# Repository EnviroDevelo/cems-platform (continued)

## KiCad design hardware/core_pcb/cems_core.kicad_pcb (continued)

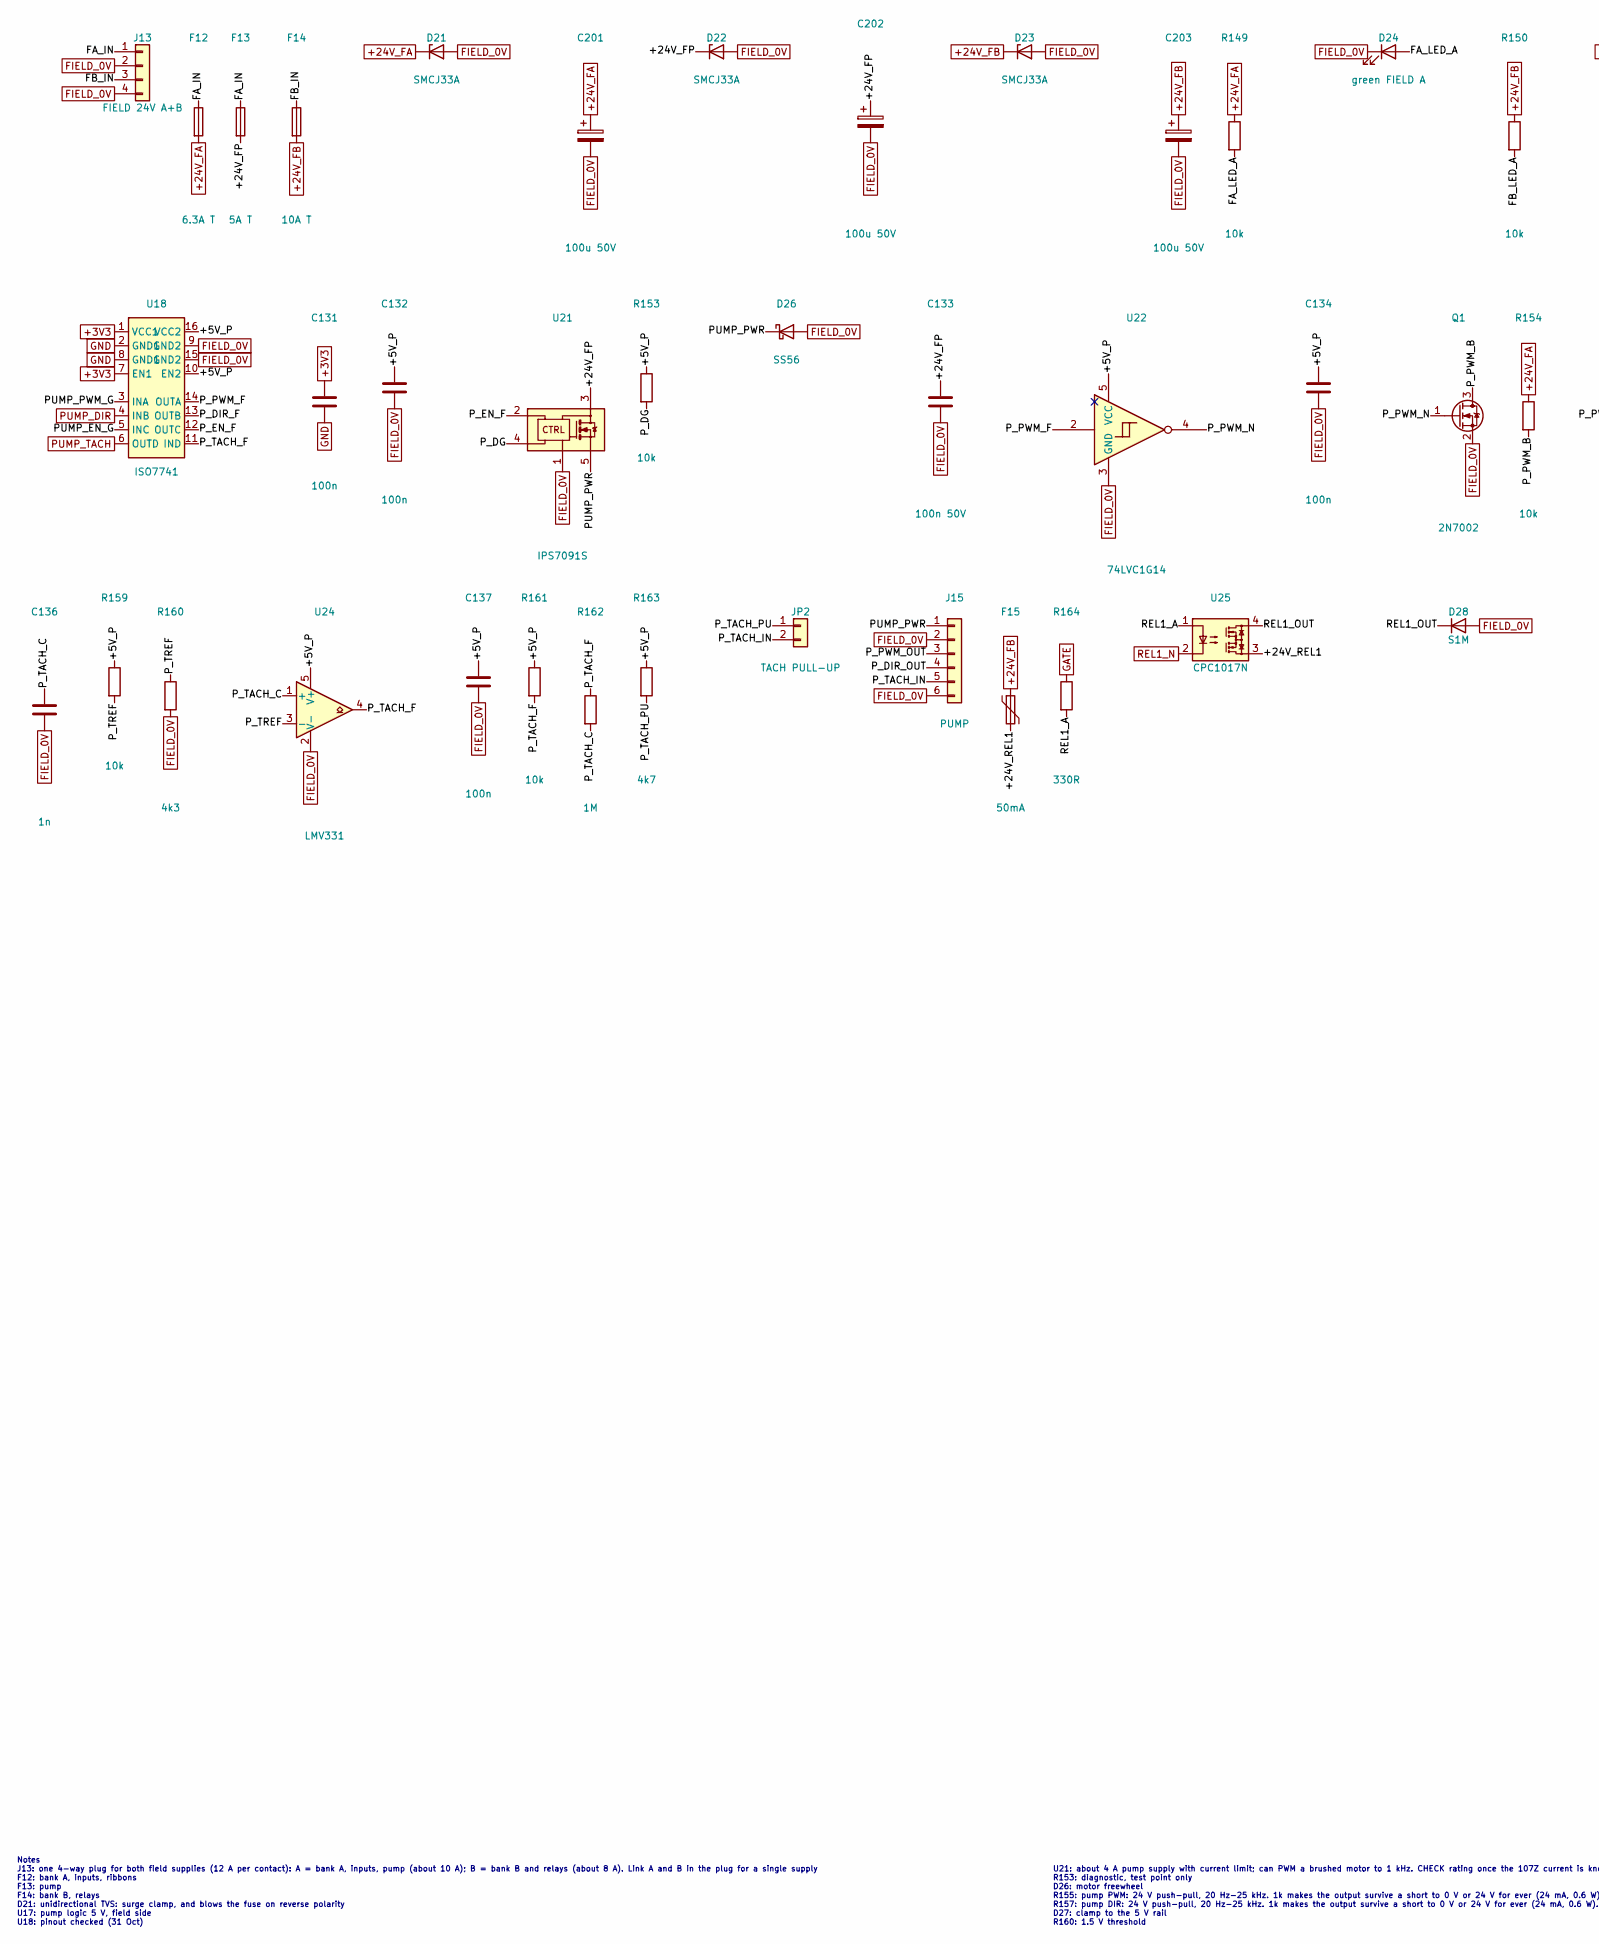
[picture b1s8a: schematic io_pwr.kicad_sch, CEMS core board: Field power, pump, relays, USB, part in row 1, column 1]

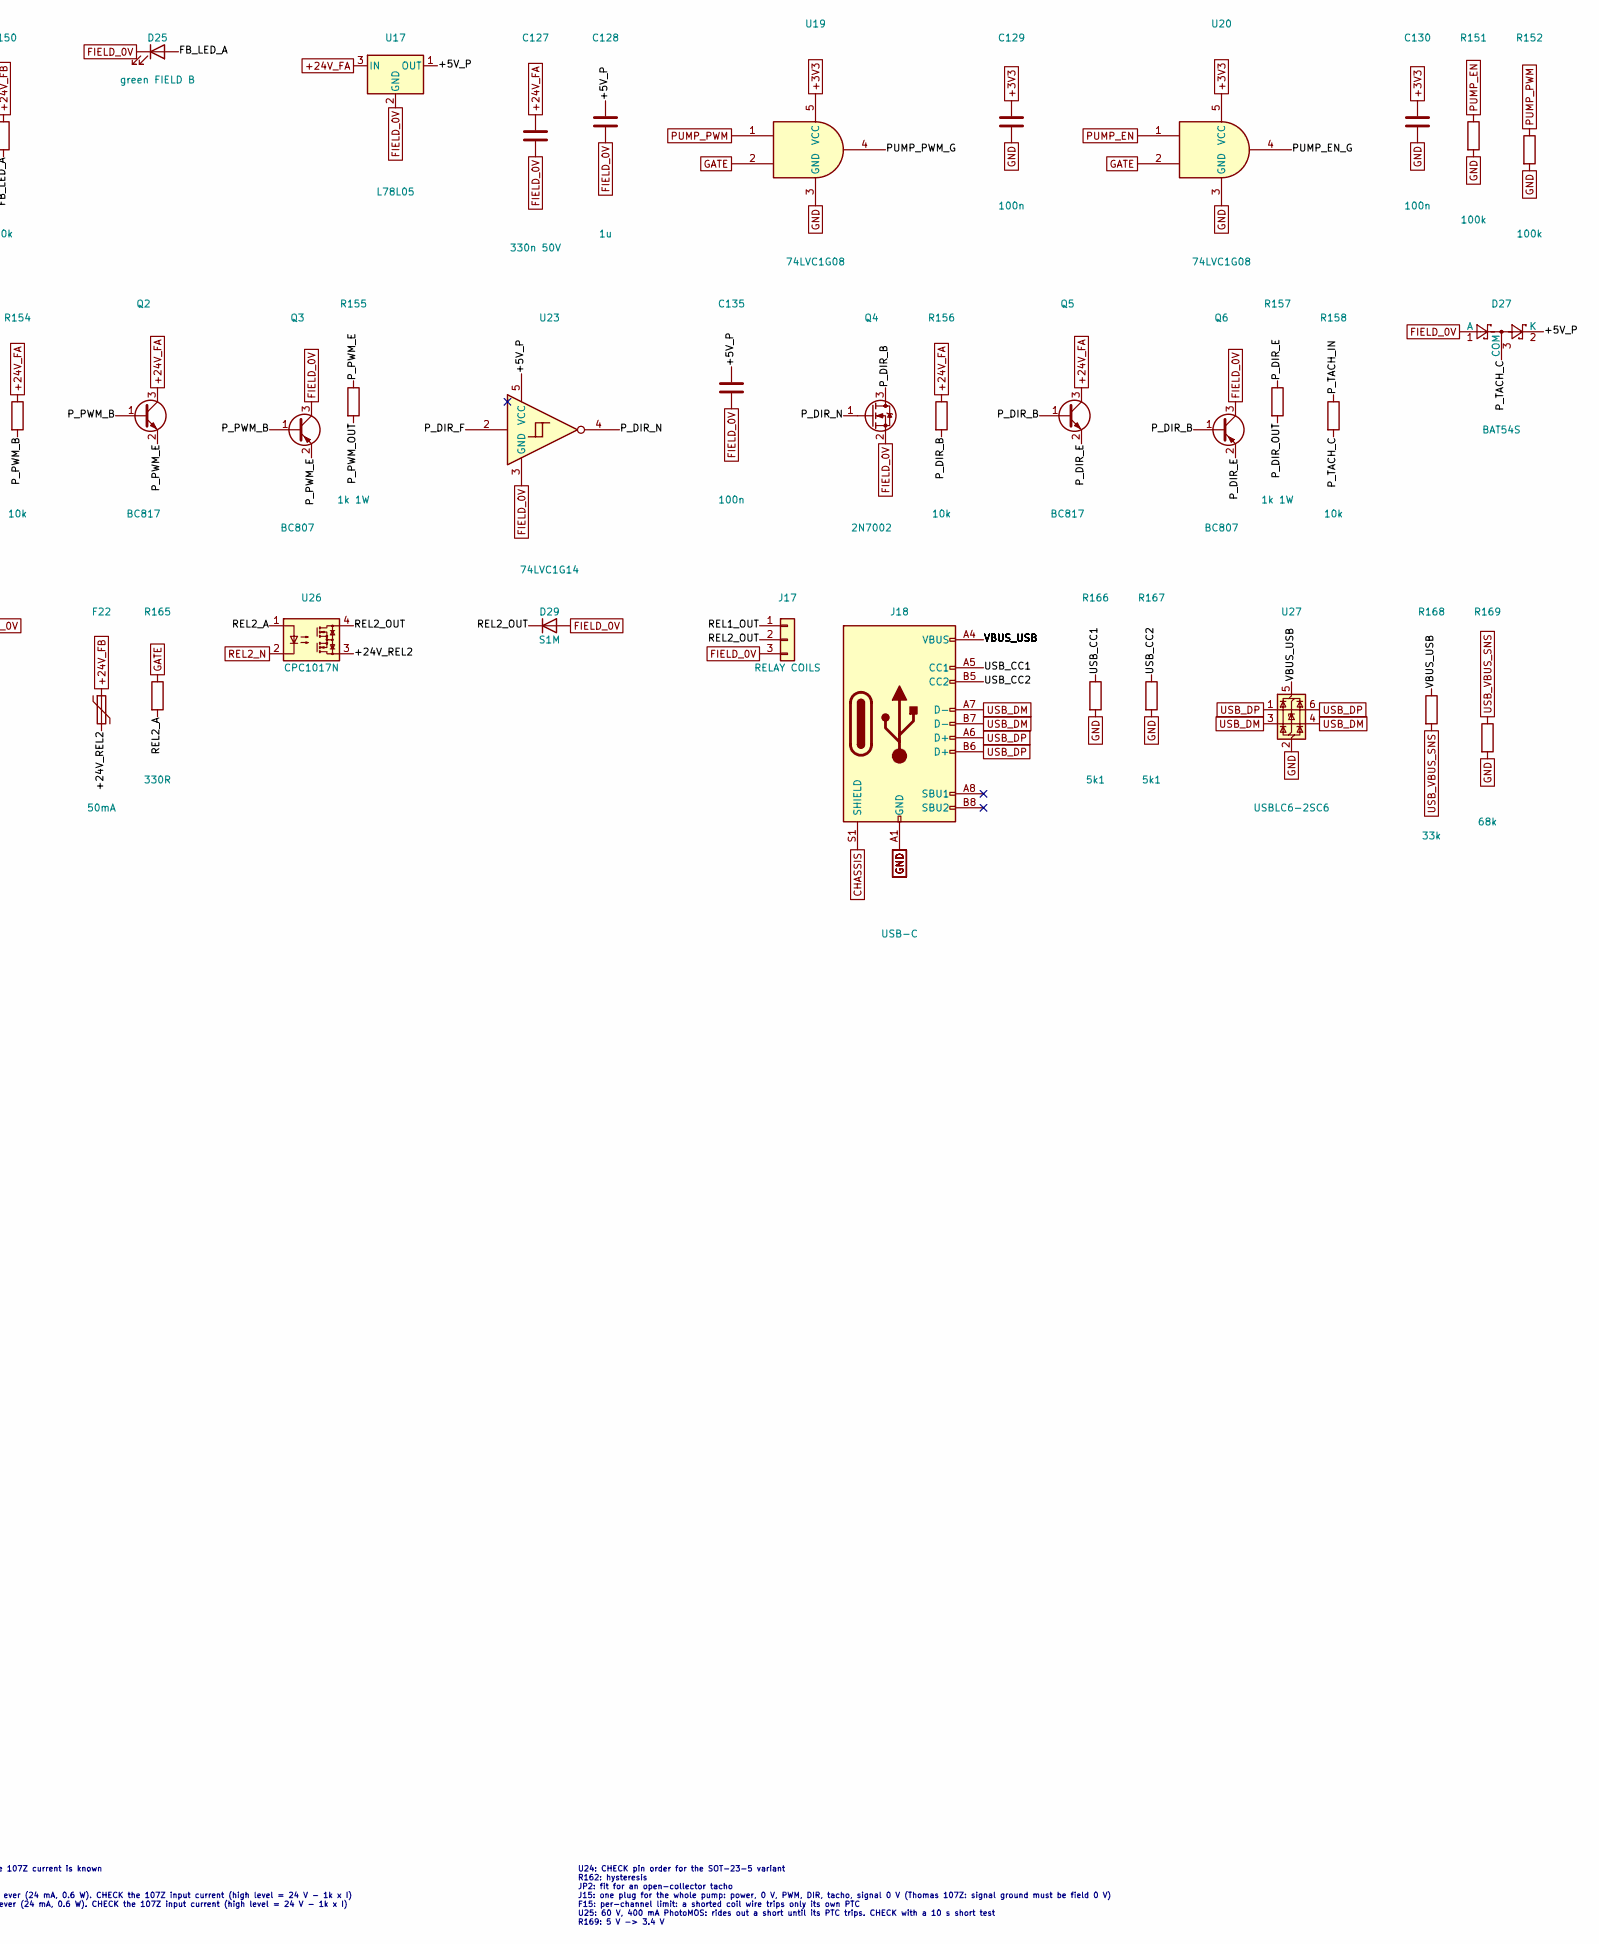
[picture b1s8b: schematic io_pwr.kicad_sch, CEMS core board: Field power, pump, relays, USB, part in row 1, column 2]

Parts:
C127: 330n 50V; C_0603_1608Metric; MPN 330n 50V
C128: 1u; C_0603_1608Metric; MPN 1u
C129, C130, C131, C132, C134, C135, C137: 100n; C_0603_1608Metric; MPN 100n
C133: 100n 50V; C_0603_1608Metric; MPN 100n 50V
C136: 1n; C_0603_1608Metric; MPN 1n
C201, C202, C203: 100u 50V; CP_Elec_10x10; MPN 100u 50V
D21, D22, D23: SMCJ33A; D_SMC; MPN SMCJ33A
D24: green FIELD A; LED_0603_1608Metric; MPN green FIELD A
D25: green FIELD B; LED_0603_1608Metric; MPN green FIELD B
D26: SS56; D_SMC; MPN SS56 (60 V, 5 A)
D27: BAT54S; SOT-23; MPN BAT54S
D28, D29: S1M; D_SMA; MPN S1M
F12: 6.3A T; Fuseholder_Littelfuse_Nano2_157x; MPN Littelfuse 0453 6.3A T NANO2 in a 157 s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
F13: 5A T; Fuseholder_Littelfuse_Nano2_157x; MPN Littelfuse 0453 5A T NANO2 in a 157 ser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
F14: 10A T; Fuseholder_Littelfuse_Nano2_157x; MPN Littelfuse 0453 10A T NANO2 in a 157 se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
F15, F22: 50mA; Fuse_1206_3216Metric; MPN Bourns MF-NSMF005-2
J13: FIELD 24V A+B; PhoenixContact_MSTBVA_2,5_4-G-5,08_1x04_P5.08mm_Vertical; MPN Phoenix MSTBVA 2,5/4-G-5,08 + coded, la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
J15: PUMP; PhoenixContact_MSTBVA_2,5_6-G-5,08_1x06_P5.08mm_Vertical; MPN Phoenix MSTBVA 2,5/6-G-5,08 + coded, la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
J17: RELAY COILS; PhoenixContact_MSTBVA_2,5_3-G-5,08_1x03_P5.08mm_Vertical; MPN Phoenix MSTBVA 2,5/3-G-5,08 + coded, la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
J18: USB-C; USB_C_Receptacle_HCTL_HC-TYPE-C-16P-01A; MPN HCTL HC-TYPE-C-16P-01A (or GCT USB4105)
JP2: TACH PULL-UP; PinHeader_1x02_P2.54mm_Vertical; MPN TACH PULL-UP
Q1, Q4: 2N7002; SOT-23; MPN 2N7002
Q2, Q5: BC817; SOT-23; MPN BC817
Q3, Q6: BC807; SOT-23; MPN BC807
R149, R150, R154, R156, R158: 10k; R_0805_2012Metric; MPN 10k
R151, R152: 100k; R_0603_1608Metric; MPN 100k
R153, R159, R161: 10k; R_0603_1608Metric; MPN 10k
R155, R157: 1k 1W; R_2512_6332Metric; MPN anti-surge 2512, 1 W
R160: 4k3; R_0603_1608Metric; MPN 4k3
R162: 1M; R_0603_1608Metric; MPN 1M
R163: 4k7; R_0603_1608Metric; MPN 4k7
R164, R165: 330R; R_0603_1608Metric; MPN 330R
R166, R167: 5k1; R_0603_1608Metric; MPN 5k1
R168: 33k; R_0603_1608Metric; MPN 33k
R169: 68k; R_0603_1608Metric; MPN 68k
U17: L78L05; SOT-89-3; MPN L78L05ACUTR
U18: ISO7741; SOIC-16W_7.5x10.3mm_P1.27mm; MPN TI ISO7741FDWR (F: outputs low when sid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
U19, U20: 74LVC1G08; SOT-23-5; MPN SN74LVC1G08DBVR
U21: IPS7091S; TO-263-5_TabPin3; MPN Infineon IPS7091SPBF
U22, U23: 74LVC1G14; SOT-23-5; MPN SN74LVC1G14DBVR
U24: LMV331; SOT-23-5; MPN LMV331IDBVR
U25, U26: CPC1017N; SOP-4_3.8x4.1mm_P2.54mm; MPN IXYS CPC1014NTR
U27: USBLC6-2SC6; SOT-23-6; MPN USBLC6-2SC6

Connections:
+3V3: C129.1, C130.1, C131.1, U18.1 (VCC1), U18.7 (EN1), U19.5 (VCC), U20.5 (VCC); also elsewhere on the board
+5V_P: C128.1, C132.1, C134.1, C135.1, C137.1, D27.2 (K), R153.1, R159.1, R161.1, R163.1, U17.1 (OUT), U18.10 (EN2), U18.16 (VCC2), U22.5 (VCC), U23.5 (VCC), U24.5 (V+)
+24V_FA: C127.1, C201.1, D21.1 (K), F12.2, Q2.3 (C), Q5.3 (C), R149.1, R154.1, R156.1, U17.3 (IN); also elsewhere on the board
+24V_FB: C203.1, D23.1 (K), F14.2, F15.1, F22.1, R150.1; also elsewhere on the board
+24V_FP: C133.1, C202.1, D22.1 (K), F13.2, U21.3 (VCC)
+24V_REL1: F15.2, U25.3
+24V_REL2: F22.2, U26.3
CHASSIS: J18.S1 (SHIELD); also elsewhere on the board
FA_IN: F12.1, F13.1, J13.1
FA_LED_A: D24.2 (A), R149.2
FB_IN: F14.1, J13.3
FB_LED_A: D25.2 (A), R150.2
FIELD_0V: C127.2, C128.2, C132.2, C133.2, C134.2, C135.2, C136.2, C137.2, C201.2, C202.2, C203.2, D21.2 (A), D22.2 (A), D23.2 (A), D24.1 (K), D25.1 (K), D26.2 (A), D27.1 (A), D28.2 (A), D29.2 (A), J13.2, J13.4, J15.2, J15.6, J17.3, Q1.2 (S), Q3.3 (C), Q4.2 (S), Q6.3 (C), R160.2, U17.2 (GND), U18.9 (GND2), U18.15 (GND2), U21.1 (GND), U22.3 (GND), U23.3 (GND), U24.2 (V-); also elsewhere on the board
GATE: R164.1, R165.1, U19.2, U20.2; also elsewhere on the board
GND: C129.2, C130.2, C131.2, J18.A1 (GND), J18.A12 (GND), J18.B1 (GND), J18.B12 (GND), R151.2, R152.2, R166.2, R167.2, R169.2, U18.2 (GND1), U18.8 (GND1), U19.3 (GND), U20.3 (GND), U27.2 (GND); also elsewhere on the board
PUMP_DIR: U18.4 (INB); also elsewhere on the board
PUMP_EN: R151.1, U20.1; also elsewhere on the board
PUMP_EN_G: U18.5 (INC), U20.4
PUMP_PWM: R152.1, U19.1; also elsewhere on the board
PUMP_PWM_G: U18.3 (INA), U19.4
PUMP_PWR: D26.1 (K), J15.1, U21.5 (OUT)
PUMP_TACH: U18.6 (OUTD); also elsewhere on the board
P_DG: R153.2, U21.4 (DG)
P_DIR_B: Q4.3 (D), Q5.1 (B), Q6.1 (B), R156.2
P_DIR_E: Q5.2 (E), Q6.2 (E), R157.1
P_DIR_F: U18.13 (OUTB), U23.2
P_DIR_N: Q4.1 (G), U23.4
P_DIR_OUT: J15.4, R157.2
P_EN_F: U18.12 (OUTC), U21.2 (IN)
P_PWM_B: Q1.3 (D), Q2.1 (B), Q3.1 (B), R154.2
P_PWM_E: Q2.2 (E), Q3.2 (E), R155.1
P_PWM_F: U18.14 (OUTA), U22.2
P_PWM_N: Q1.1 (G), U22.4
P_PWM_OUT: J15.3, R155.2
P_TACH_C: C136.1, D27.3 (COM), R158.2, R162.2, U24.1 (+)
P_TACH_F: R161.2, R162.1, U18.11 (IND), U24.4
P_TACH_IN: J15.5, JP2.2, R158.1
P_TACH_PU: JP2.1, R163.2
P_TREF: R159.2, R160.1, U24.3 (-)
REL1_A: R164.2, U25.1
REL1_N: U25.2; also elsewhere on the board
REL1_OUT: D28.1 (K), J17.1, U25.4
REL2_A: R165.2, U26.1
REL2_N: U26.2; also elsewhere on the board
REL2_OUT: D29.1 (K), J17.2, U26.4
USB_CC1: J18.A5 (CC1), R166.1
USB_CC2: J18.B5 (CC2), R167.1
USB_DM: J18.A7 (D-), J18.B7 (D-), U27.3 (I/O2), U27.4 (I/O2); also elsewhere on the board
USB_DP: J18.A6 (D+), J18.B6 (D+), U27.1 (I/O1), U27.6 (I/O1); also elsewhere on the board
USB_VBUS_SNS: R168.2, R169.1; also elsewhere on the board
VBUS_USB: J18.A4 (VBUS), J18.A9 (VBUS), J18.B4 (VBUS), J18.B9 (VBUS), R168.1, U27.5 (VBUS)

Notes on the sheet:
Notes J13: one 4-way plug for both field supplies (12 A per contact): A = bank A, inputs, pump (about 10 A); B = bank B and relays (about 8 A). Link A and B in the plug for a single supply F12: bank A, inputs, ribbons F13: pump F14: bank B, relays D21: unidirectional TVS: surge clamp, and blows the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
U21: about 4 A pump supply with current limit; can PWM a brushed motor to 1 kHz. CHECK rating once the 107Z current is known R153: diagnostic, test point only D26: motor freewheel R155: pump PWM: 24 V push-pull, 20 Hz-25 kHz. 1k makes the output survive a short to 0 V or 24 V for ever (24 mA, 0.6 W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
U24: CHECK pin order for the SOT-23-5 variant R162: hysteresis JP2: fit for an open-collector tacho J15: one plug for the whole pump: power, 0 V, PWM, DIR, tacho, signal 0 V (Thomas 107Z: signal ground must be field 0 V) F15: per-channel limit: a shorted coil wire trips only its own PTC U25: 60 V, 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

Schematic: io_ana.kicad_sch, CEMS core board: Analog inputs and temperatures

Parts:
C138, C140, C141, C143, C144, C146, C148, C149, C156, C158, C159, C161, C164, C166, C168, C170: 100n; C_0603_1608Metric; MPN 100n
C139, C142, C157, C160: 10u; C_0805_2012Metric; MPN 10u
C145, C147, C165, C167, C169, C172, C174: 1u; C_0603_1608Metric; MPN 1u
C150, C151, C152, C153, C154, C155: 10n C0G; C_0603_1608Metric; MPN 10n C0G
C162, C163: 10u 50V; C_1210_3225Metric; MPN 10u 50V
C171: 330n 50V; C_0603_1608Metric; MPN 330n 50V
C173, C175: 1u 25V; C_0805_2012Metric; MPN 1u 25V
C176: 4u7 25V; C_0805_2012Metric; MPN 4u7 25V
C177: 10u 25V; C_0805_2012Metric; MPN 10u 25V
D49: SMAJ5.0A; D_SMA; MPN SMAJ5.0A
D50: SMAJ11A; D_SMA; MPN SMAJ11A
F16, F17, F18, F19, F20, F21: CCR 30mA; D_PowerDI-123; MPN Diodes AL5809-30P1-7 (60 V, 30 mA)
FB10, FB11: 600R@100MHz; L_0603_1608Metric; MPN 600R@100MHz
J19: TEMP1; PhoenixContact_MCV_1,5_5-G-3.5_1x05_P3.50mm_Vertical; MPN Phoenix MCV 1,5/5-G-3,5 + coded, labell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
J20: TEMP2; PhoenixContact_MCV_1,5_5-G-3.5_1x05_P3.50mm_Vertical; MPN Phoenix MCV 1,5/5-G-3,5 + coded, labell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
J21: TEMP3; PhoenixContact_MCV_1,5_5-G-3.5_1x05_P3.50mm_Vertical; MPN Phoenix MCV 1,5/5-G-3,5 + coded, labell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
J22: AI 1-2; PhoenixContact_MCV_1,5_6-G-3.5_1x06_P3.50mm_Vertical; MPN Phoenix MCV 1,5/6-G-3,5 + coded, labell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
J23: AI 3-4; PhoenixContact_MCV_1,5_6-G-3.5_1x06_P3.50mm_Vertical; MPN Phoenix MCV 1,5/6-G-3,5 + coded, labell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
J24: AI 5-6; PhoenixContact_MCV_1,5_6-G-3.5_1x06_P3.50mm_Vertical; MPN Phoenix MCV 1,5/6-G-3,5 + coded, labell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
J25: SENSORS; PhoenixContact_MCV_1,5_7-G-3.5_1x07_P3.50mm_Vertical; MPN Phoenix MCV 1,5/7-G-3,5 + coded, labell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
R170, R171, R182, R183: 10k; R_0603_1608Metric; MPN 10k
R172: 5k11 0.1%; R_0603_1608Metric; MPN 5k11 0.1%
R173, R174, R175, R176, R177, R178: 10M; R_0603_1608Metric; MPN 10M
R179, R180, R181: 100R; R_0603_1608Metric; MPN 100R
R184, R185: 250R 0.1%; R_1206_3216Metric; MPN Vishay PTN1206 0.4 W, 10 ppm/K thin film
R186: 100k; R_0603_1608Metric; MPN 100k
R187: 240R 1%; R_0603_1608Metric; MPN 240R 1%
R188: 2k26 1%; R_0603_1608Metric; MPN 2k26 1%
R189: 3k; R_0603_1608Metric; MPN 3k
R190, R191: 100k 0.1%; R_0603_1608Metric; MPN 100k 0.1%
R192: 1M; R_0603_1608Metric; MPN 1M
U28, U31: ISOW7741; SOIC-20W_7.5x12.8mm_P1.27mm; MPN TI ISOW7741DFMR
U29, U32: 74LVC1G04; SOT-23-5; MPN SN74LVC1G04DBVR
U30: ADS124S08; TQFP-32_7x7mm_P0.8mm; MPN TI ADS124S08IPBSR
U33: ITX2424SA; Converter_DCDC_XP_POWER-ITXxxxxSA_THT; MPN XP Power ITX2424SA (6 W, 1.6 kV)
U34: AD4112; LFCSP-40-1EP_6x6mm_P0.5mm_EP3.9x3.9mm; MPN ADI AD4112BCPZ
U35: L78L05; SOT-89-3; MPN L78L05ACUTR
U36: LM317L; SOIC-8_3.9x4.9mm_P1.27mm; MPN LM317LDR
U37: REF5010; SOIC-8_3.9x4.9mm_P1.27mm; MPN REF5010AIDR (0.05 %, 3 ppm/K)
U38: LT3045; MSOP-12-1EP_3x4mm_P0.65mm_EP1.65x2.85mm; MPN LT3045EMSE#PBF

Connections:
+3V3: C138.1, C141.1, C156.1, C159.1, R170.1, R182.1, U28.1 (V_{IO}), U29.5 (VCC), U31.1 (V_{IO}), U32.5 (VCC); also elsewhere on the board
+3V3_T: C142.1, C143.1, C144.1, FB10.1, R171.1, U28.12 (V_{ISOOUT}), U28.14 (EN_IO2), U28.20 (V_{ISOIN}), U30.15 (IOVDD), U30.16 (DVDD)
+3V3_TA: C145.1, C146.1, FB10.2, U30.26 (AVDD)
+5V: C139.1, C140.1, C157.1, C158.1, U28.9 (V_{DD}), U31.9 (V_{DD}); also elsewhere on the board
+5V_AI: C160.1, C161.1, C164.1, FB11.1, R183.1, U31.12 (V_{ISOOUT}), U31.13 (VSEL), U31.14 (EN_IO2), U31.20 (V_{ISOIN}), U34.19 (~SYNC), U34.20 (IOVDD)
+5V_AIA: C165.1, C166.1, FB11.2, U34.9 (AVDD)
+5V_LVL: C172.1, D49.1 (K), J25.1, U34.27 (VIN5), U35.1 (OUT)
+10V_FLOW: C177.1, D50.1 (K), J25.4, R190.1, U38.10 (OUTS), U38.11 (OUT), U38.12 (OUT)
+13V_AI: C173.1, C176.1, R187.1, U36.2 (VO), U36.3 (VO), U36.6 (VO), U36.7 (VO), U37.2 (Vin), U38.1 (IN), U38.2 (IN), U38.3 (IN), U38.4 (EN/UV), U38.7 (PGFB)
+24V: C162.1, U33.2 (+Vin); also elsewhere on the board
+24V_AI: C163.1, C171.1, F16.2 (A), F17.2 (A), F18.2 (A), F19.2 (A), F20.2 (A), F21.2 (A), U33.6 (+Vout), U35.3 (IN), U36.1 (VI)
AI1_IN: J22.2, U34.34 (IIN0+)
AI2_IN: J22.5, U34.35 (IIN1+)
AI3_IN: J23.2, U34.36 (IIN2+)
AI4_IN: J23.5, U34.37 (IIN3+)
AI5_IN: J24.2, R184.1, U34.2 (VIN0)
AI6_IN: J24.5, R185.1, U34.3 (VIN1)
AI_ADJ: R187.2, R188.1, U36.4 (ADJ)
AI_CS: U31.17 (OUTC), U34.17 (~CS)
AI_DIN: U31.18 (OUTB), U34.15 (DIN)
AI_DOUT: U31.16 (IND), U34.14 (DOUT/~RDY)
AI_EN1: U31.7 (EN_IO1), U32.4
AI_ENFLT: R182.2, U31.8 (EN/FLT)
AI_ERR: R183.2, U34.18 (~ERROR)
AI_REF: C170.1, U34.6 (REFOUT), U34.40 (REF+)
AI_REGCAPA: C167.1, C168.1, U34.7 (REGCAPA)
AI_REGCAPD: C169.1, U34.22 (REGCAPD)
AI_SCLK: U31.19 (OUTA), U34.16 (SCLK)
CS_AI: U31.4 (INC), U32.2; also elsewhere on the board
CS_T: U28.4 (INC), U29.2; also elsewhere on the board
FLOW_ILIM: R189.1, U38.6 (ILIM)
FLOW_SIG: J25.5, R192.1, U34.5 (VIN3)
GND: C138.2, C139.2, C140.2, C141.2, C156.2, C157.2, C158.2, C159.2, C162.2, U28.6 (GNDIO), U28.10 (GND1), U29.3 (GND), U31.6 (GNDIO), U31.10 (GND1), U32.3 (GND), U33.1 (-Vin); also elsewhere on the board
GND_AI: C160.2, C161.2, C163.2, C164.2, C165.2, C166.2, C167.2, C168.2, C169.2, C170.2, C171.2, C172.2, C173.2, C174.2, C175.2, C176.2, C177.2, D49.2 (A), D50.2 (A), J22.3, J22.6, J23.3, J23.6, J24.3, J24.6, J25.3, J25.6, J25.7, R184.2, R185.2, R186.2, R188.2, R189.2, R191.2, R192.2, U31.11 (GND2), U31.15 (GISOIN), U33.7 (-Vout), U34.1 (VINCOM), U34.8 (AVSS), U34.11 (VBIAS-), U34.21 (DGND), U34.30 (IIN3-), U34.31 (IIN2-), U34.32 (IIN1-), U34.33 (IIN0-), U34.39 (REF-), U34.41 (EP), U35.2 (GND), U37.4 (GND), U38.9 (GND), U38.13 (GND)
GND_T: C142.2, C143.2, C144.2, C145.2, C146.2, C147.2, C148.2, C149.2, R172.2, U28.11 (GND2), U28.13 (VSEL), U28.15 (GISOIN), U30.8 (START/SYNC), U30.14 (DGND), U30.17 (CLK), U30.24 (REFCOM), U30.27 (AVSS), U30.28 (AVSS-SW), U30.29 (REFN0)
LOOP1: F16.1 (K), J22.1
LOOP2: F17.1 (K), J22.4
LOOP3: F18.1 (K), J23.1
LOOP4: F19.1 (K), J23.4
LOOP5: F20.1 (K), J24.1
LOOP6: F21.1 (K), J24.4
LVL_SIG: J25.2, R186.1, U34.4 (VIN2)
REF10: C175.1, U37.6 (Vout), U38.8 (SET)
REF10_NR: C174.1, U37.5 (Trim/NR)
SPI4_MISO: U28.5 (OUTD), U31.5 (OUTD); also elsewhere on the board
SPI4_MOSI: U28.3 (INB), U31.3 (INB); also elsewhere on the board
SPI4_SCK: U28.2 (INA), U31.2 (INA); also elsewhere on the board
T1_N: C150.2, J19.2, R173.1, U30.6 (AIN1)
T1_P: C150.1, J19.1, U30.7 (AIN0)
T2_N: C151.2, J19.4, R174.1, U30.4 (AIN3)
T2_P: C151.1, J19.3, U30.5 (AIN2)
T3_N: C152.2, J20.2, R175.1, U30.2 (AIN5)
T3_P: C152.1, J20.1, U30.3 (AIN4)
T4_N: C153.2, J20.4, R176.1, U30.31 (AIN7/REFN1)
T4_P: C153.1, J20.3, U30.32 (AIN6/REFP1)
T5_N: C154.2, J21.2, R177.1, U30.21 (AIN9)
T5_P: C154.1, J21.1, U30.22 (AIN8)
T6_N: C155.2, J21.4, R178.1, U30.19 (AIN11)
T6_P: C155.1, J21.3, U30.20 (AIN10)
T_AINCOM: C149.1, R173.2, R174.2, R175.2, R176.2, R177.2, R178.2, U30.1 (AINCOM)
T_CS: U28.17 (OUTC), U30.9 (~CS)
T_DIN: U28.18 (OUTB), U30.10 (DIN)
T_DOUT: U28.16 (IND), U30.12 (DOUT/~DRDY)
T_EN1: U28.7 (EN_IO1), U29.4
T_ENFLT: R170.2, U28.8 (EN/FLT)
T_REFOUT: C147.1, U30.23 (REFOUT)
T_REFP: C148.1, R172.1, R179.2, R180.2, R181.2, U30.30 (REFP0)
T_RST: R171.2, U30.18 (~RESET)
T_RTN1: J19.5, R179.1
T_RTN2: J20.5, R180.1
T_RTN3: J21.5, R181.1
T_SCLK: U28.19 (OUTA), U30.11 (SCLK)
V10_MON: R190.2, R191.1, U34.26 (VIN4)

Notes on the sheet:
Notes U28: VSEL to GND2 = 3.3 V out (140 mA) R170: EN/FLT high (VIO level) enables the DC/DC; reads low on a fault U30: pinout checked (SBAS660, 31 Oct). Internal 4.096 MHz clock (CLK to DGND), START low (conversions by command), DOUT/DRDY on one pin C147: REFOUT to REFCOM R172: RTD reference resis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
J21: T5 +/-, T6 +/-, RTD return U31: VSEL to VISOOUT = 5 V out (110 mA) R182: EN/FLT high (VIO level) enables the DC/DC; reads low on a fault U33: loop power 6 x 22 mA + level + mass-flow supply, about 4 W U34: internal oscillator and 2.5 V reference. VIN0/1: 4-20 mA ch 5/6 on shunts; VIN2 level; V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
J24: per channel: 24 V loop, IN, 0 V (2-wire or 4-wire transmitters) U35: level sensor 5 V, internal current limit R186: defined level when unplugged U36: 13 V pre-regulator, about 0.5 W: copper on the VO pins R188: 1.25 x (1 + 2260/240) = 13.0 V U38: SET driven by the REF5010 (no RSET). CHECK PGFB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

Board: 4 copper layers, 434 parts (1 on the bottom side), 314 nets, no tracks yet.

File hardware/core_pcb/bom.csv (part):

Qty,References,Value,Footprint,MPN / note,Fitted
1,BT1,CR2032,BatteryHolder_Keystone_3034_1x20mm,Keystone 3034 holder + CR2032,yes
1,C1,47u 63V,CP_Elec_8x10,,yes
1,C2,2u2 100V,C_1210_3225Metric,,yes
1,C3,100n 100V,C_0603_1608Metric,,yes
60,C4 C13 C14 C20 C21 C22 C23 C24 C25 C28 C35 C36 C37 C41 C42 C43 C49 C51 C52 C53 C54 C55 C56 C57 C64 C70 C71 C73 C75 C76 C101 C102 C103 C105 C118 C121 C125 C129 C130 C131 C132 C134 C135 C137 C138 C140 C141 C143 C144 C146 C148 C149 C156 C158 C159 C161 C164 C166 C168 C170,100n,C_0603_1608Metric,,yes
1,C5,33n,C_0603_1608Metric,,yes
1,C6,100p,C_0603_1608Metric,,yes
2,C7 C8,22u 10V,C_1210_3225Metric,,yes
1,C9,10u 10V,C_0805_2012Metric,,yes
1,C10,22p,C_0603_1608Metric,,yes
2,C11 C12,22u 10V,C_1206_3216Metric,,yes
3,C15 C16 C17,4n7 2kV,C_1812_4532Metric,,yes
2,C18 C19,470u 63V,CP_Radial_D12.5mm_P5.00mm,"470 uF 63 V, 105 C, low ESR, 12.5 mm radial",yes
2,C26 C59,4u7,C_0805_2012Metric,,yes
13,C27 C40 C44 C77 C119 C128 C145 C147 C165 C167 C169 C172 C174,1u,C_0603_1608Metric,,yes
2,C29 C30,2u2,C_0603_1608Metric,,yes
2,C31 C32,12p,C_0603_1608Metric,,yes
2,C33 C34,6p8,C_0603_1608Metric,,yes
1,C45,470p,C_0603_1608Metric,,yes
2,C46 C47,33p,C_0603_1608Metric,,yes
1,C48,22n,C_0603_1608Metric,,yes
8,C50 C72 C74 C122 C139 C142 C157 C160,10u,C_0805_2012Metric,,yes
2,C58 C63,10n,C_0603_1608Metric,,yes
2,C60 C61,18p,C_0603_1608Metric,,yes
1,C62,6n8,C_0603_1608Metric,,yes
1,C104,2u2,C_0805_2012Metric,,yes
1,C106,1u 50V,C_0805_2012Metric,,yes
1,C107,470n,C_0603_1608Metric,,yes
1,C108,2u2 50V,C_1210_3225Metric,,yes
3,C109 C120 C133,100n 50V,C_0603_1608Metric,,yes
8,C110 C111 C112 C113 C114 C115 C116 C117,12n 100V,C_0603_1608Metric,,yes
2,C123 C124,470n 50V,C_0805_2012Metric,,yes
1,C126,100n,C_0805_2012Metric,,yes
2,C127 C171,330n 50V,C_0603_1608Metric,,yes
1,C136,1n,C_0603_1608Metric,,yes
6,C150 C151 C152 C153 C154 C155,10n C0G,C_0603_1608Metric,,yes
2,C162 C163,10u 50V,C_1210_3225Metric,,yes
2,C173 C175,1u 25V,C_0805_2012Metric,,yes
1,C176,4u7 25V,C_0805_2012Metric,,yes
1,C177,10u 25V,C_0805_2012Metric,,yes
4,C200 C201 C202 C203,100u 50V,CP_Elec_10x10,,yes
1,D1,SS16,D_SMA,"SS16 (60 V, 1 A)",yes
1,D2,SMDJ33CA,D_SMC,SMDJ33CA (3 kW),yes
1,D3,B260A,D_SMA,"B260A-13 (60 V, 2 A)",yes
1,D10,green RUN,LED_0603_1608Metric,,yes
1,D11,red FAULT,LED_0603_1608Metric,,yes
3,D21 D22 D23,SMCJ33A,D_SMC,SMCJ33A,yes
1,D24,green FIELD A,LED_0603_1608Metric,,yes
1,D25,green FIELD B,LED_0603_1608Metric,,yes
1,D26,SS56,D_SMC,"SS56 (60 V, 5 A)",yes
1,D27,BAT54S,SOT-23,,yes
10,D28 D29 D31 D32 D33 D34 D35 D36 D37 D38,S1M,D_SMA,,yes
1,D49,SMAJ5.0A,D_SMA,SMAJ5.0A,yes
1,D50,SMAJ11A,D_SMA,SMAJ11A,yes
1,F1,2A T,Fuse_1206_3216Metric,,yes
1,F10,0.75A,Fuse_1812_4532Metric,Bourns MF-MSMF075-2,yes
1,F12,6.3A T,Fuseholder_Littelfuse_Nano2_157x,Littelfuse 0453 6.3A T NANO2 in a 157 series holder,yes
1,F13,5A T,Fuseholder_Littelfuse_Nano2_157x,Littelfuse 0453 5A T NANO2 in a 157 series holder,yes
1,F14,10A T,Fuseholder_Littelfuse_Nano2_157x,Littelfuse 0453 10A T NANO2 in a 157 series holder,yes
2,F15 F22,50mA,Fuse_1206_3216Metric,Bourns MF-NSMF005-2,yes
6,F16 F17 F18 F19 F20 F21,CCR 30mA,D_PowerDI-123,"Diodes AL5809-30P1-7 (60 V, 30 mA)",yes
1,F23,0.5A,Fuse_1206_3216Metric,Bourns MF-NSMF050-2,yes
1,F24,0.1A,Fuse_1206_3216Metric,Bourns MF-NSMF010-2,yes
6,FB1 FB2 FB3 FB4 FB10 FB11,600R@100MHz,L_0603_1608Metric,,yes
1,J1,24VDC IN,"TerminalBlock_Phoenix_MKDS-1,5-3-5.08_1x03_P5.08mm_Horizontal",,yes
1,J2,CLIENT,RJ45_Wuerth_7499010121A_Horizontal,"Wurth 7499010121A (MagJack, 1500 Vrms, LEDs)",yes
1,J3,I/O ONLY,RJ45_Wuerth_7499010121A_Horizontal,Wurth 7499010121A,yes
1,J4,RVT70 RiBUS,Hirose_FH12-20S-0.5SH_1x20-1MP_P0.50mm_Horizontal,Hirose FH12-20S-0.5SH(55),yes
1,J5,SWD,PinHeader_2x05_P1.27mm_Vertical_SMD,,yes
1,J6,SERVICE UART,PinHeader_1x06_P2.54mm_Vertical,,yes
1,J7,ROLE,PinHeader_1x03_P2.54mm_Vertical,,yes
1,J10,DIGITAL I/O IDC40,IDC-Header_2x20_P2.54mm_Latch_Vertical,"Wurth 61204022821 (WR-BHD 40-way, long latches, 3 A). CHECK MPN",yes
1,J11,BANK B,"PhoenixContact_MCV_1,5_10-G-3.81_1x10_P3.81mm_Vertical","Phoenix MCV 1,5/10-G-3,81 + coded, labelled plug",yes
1,J13,FIELD 24V A+B,"PhoenixContact_MSTBVA_2,5_4-G-5,08_1x04_P5.08mm_Vertical","Phoenix MSTBVA 2,5/4-G-5,08 + coded, labelled plug; coding key at pin 3 (header CR-MSTB, plug coded to match). CHECK coding parts",yes
1,J15,PUMP,"PhoenixContact_MSTBVA_2,5_6-G-5,08_1x06_P5.08mm_Vertical","Phoenix MSTBVA 2,5/6-G-5,08 + coded, labelled plug; coding key at pin 1, 3, 5 (header CR-MSTB, plug coded to match). CHECK coding parts",yes
1,J17,RELAY COILS,"PhoenixContact_MSTBVA_2,5_3-G-5,08_1x03_P5.08mm_Vertical","Phoenix MSTBVA 2,5/3-G-5,08 + coded, labelled plug; coding key at pin 1 (header CR-MSTB, plug coded to match). CHECK coding parts",yes
1,J18,USB-C,USB_C_Receptacle_HCTL_HC-TYPE-C-16P-01A,HCTL HC-TYPE-C-16P-01A (or GCT USB4105),yes
1,J19,TEMP1,"PhoenixContact_MCV_1,5_5-G-3.5_1x05_P3.50mm_Vertical","Phoenix MCV 1,5/5-G-3,5 + coded, labelled plug; coding key at pin 1 (header CR-MC, plug coded to match). CHECK coding parts",yes
1,J20,TEMP2,"PhoenixContact_MCV_1,5_5-G-3.5_1x05_P3.50mm_Vertical","Phoenix MCV 1,5/5-G-3,5 + coded, labelled plug; coding key at pin 1 (header CR-MC, plug coded to match). CHECK coding parts",yes
1,J21,TEMP3,"PhoenixContact_MCV_1,5_5-G-3.5_1x05_P3.50mm_Vertical","Phoenix MCV 1,5/5-G-3,5 + coded, labelled plug; coding key at pin 1 (header CR-MC, plug coded to match). CHECK coding parts",yes
1,J22,AI 1-2,"PhoenixContact_MCV_1,5_6-G-3.5_1x06_P3.50mm_Vertical","Phoenix MCV 1,5/6-G-3,5 + coded, labelled plug; coding key at pin 3 (header CR-MC, plug coded to match). CHECK coding parts",yes
1,J23,AI 3-4,"PhoenixContact_MCV_1,5_6-G-3.5_1x06_P3.50mm_Vertical","Phoenix MCV 1,5/6-G-3,5 + coded, labelled plug; coding key at pin 3 (header CR-MC, plug coded to match). CHECK coding parts",yes
1,J24,AI 5-6,"PhoenixContact_MCV_1,5_6-G-3.5_1x06_P3.50mm_Vertical","Phoenix MCV 1,5/6-G-3,5 + coded, labelled plug; coding key at pin 3 (header CR-MC, plug coded to match). CHECK coding parts",yes
1,J25,SENSORS,"PhoenixContact_MCV_1,5_7-G-3.5_1x07_P3.50mm_Vertical","Phoenix MCV 1,5/7-G-3,5 + coded, labelled plug; coding key at pin 5 (header CR-MC, plug coded to match). CHECK coding parts",yes
1,J26,SPI EXPANSION,IDC-Header_2x05_P2.54mm_Latch_Vertical,Wurth 61201021621 (WR-BHD 10-way latched) CHECK MPN,yes
1,JP1,BOOT0,PinHeader_1x02_P2.54mm_Vertical,,yes
1,JP2,TACH PULL-UP,PinHeader_1x02_P2.54mm_Vertical,,yes
1,L1,22uH,L_Bourns_SRN6045TA,Bourns SRN6045TA-220M,yes
1,L2,2u2 3A,L_Wuerth_MAPI-4030,"Wurth 74438357022 (MAPI 4030, 2.2 uH)",yes
1,L3,WE-SL2 744227,L_CommonMode_Wuerth_WE-SL2,Wurth 744227,yes
2,Q1 Q4,2N7002,SOT-23,,yes
2,Q2 Q5,BC817,SOT-23,,yes
2,Q3 Q6,BC807,SOT-23,,yes
1,R3,162k 1%,R_0603_1608Metric,,yes
1,R4,52k3 1%,R_0603_1608Metric,,yes
1,R5,10k 1%,R_0603_1608Metric,,yes
1,R6,4k99 1%,R_0603_1608Metric,,yes
2,R7 R9,100k 1%,R_0603_1608Metric,,yes
2,R8 R118,22k1 1%,R_0603_1608Metric,,yes
1,R10,8k2 1%,R_0603_1608Metric,,yes
1,R11,1M,R_1206_3216Metric,,yes
33,R20 R23 R24 R27 R28 R33 R34 R53 R54 R55 R70 R71 R72 R79 R101 R107 R108 R109 R121 R142 R143 R144 R145 R146 R147 R148 R153 R159 R161 R170 R171 R182 R183,10k,R_0603_1608Metric,,yes
3,R21 R22 R103,1k,R_0603_1608Metric,,yes
2,R30 R106,12k1 1%,R_0603_1608Metric,,yes
1,R31,22R,R_0603_1608Metric,,yes
1,R32,1k5,R_0603_1608Metric,,yes
8,R35 R36 R37 R38 R56 R57 R58 R59,49R9 1%,R_0603_1608Metric,,yes
6,R39 R40 R60 R61 R164 R165,330R,R_0603_1608Metric,,yes
13,R41 R42 R43 R44 R45 R46 R51 R52 R73 R76 R77 R78 R119,33R,R_0603_1608Metric,,yes
1,R50,12k4 1%,R_0603_1608Metric,,yes
3,R62 R162 R192,1M,R_0603_1608Metric,,yes
1,R63,0R,R_0603_1608Metric,,yes
2,R74 R75,2k2,R_0603_1608Metric,,yes
5,R102 R141 R151 R152 R186,100k,R_0603_1608Metric,,yes
1,R104,10k 0.1%,R_0603_1608Metric,,yes
1,R105,6k81 1%,R_0603_1608Metric,,yes
8,R110 R111 R112 R113 R114 R115 R116 R117,0R,R_1206_3216Metric,,yes
2,R120 R168,33k,R_0603_1608Metric,,yes
8,R122 R124 R126 R128 R130 R132 R134 R136,12k 1%,R_1206_3216Metric,,yes
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
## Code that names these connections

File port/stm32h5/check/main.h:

/* main.h - COMPILE-CHECK STUB ONLY. Stands in for the CubeMX-generated main.h so
 * the target sources can be compiled outside CubeIDE. The pin assignments here
 * are placeholders, not the DK's or the product's real pins. */
#ifndef MAIN_H
#define MAIN_H
#include "stm32h5xx_hal.h"
#define DI_01_Pin GPIO_PIN_13
#define DI_01_GPIO_Port GPIOC
#define DO_01_Pin GPIO_PIN_0
#define DO_01_GPIO_Port GPIOA
#define DO_01_ACTIVE_LOW 1
#define DO_02_Pin GPIO_PIN_1
#define DO_02_GPIO_Port GPIOA
/* compile-check both FRAM paths: define CHECK_WITH_FRAM to build the SPI driver */
#ifdef CHECK_WITH_I2C_FRAM
#define FRAM_I2C_HANDLE hi2c1
#endif
#ifdef CHECK_WITH_EVE
#define EVE_CS_Pin GPIO_PIN_6
#define EVE_CS_GPIO_Port GPIOE
#define EVE_PD_Pin GPIO_PIN_7
#define EVE_PD_GPIO_Port GPIOE
#endif
#ifdef CHECK_WITH_NOR
#define NOR_CS_Pin GPIO_PIN_5
#define NOR_CS_GPIO_Port GPIOE
#endif
#ifdef CHECK_WITH_RS485
#define BSP_RS485_HUART huart2
#endif
#ifdef CHECK_WITH_W5500
#define W5500_CS_Pin GPIO_PIN_11
#define W5500_CS_GPIO_Port GPIOE
#define W5500_RST_Pin GPIO_PIN_10
#define W5500_RST_GPIO_Port GPIOE
#define CS_EXP_Pin GPIO_PIN_3              /* the SPI expansion header (CORE_PCB.md 16): held high */
#define CS_EXP_GPIO_Port GPIOD
#define EXP_INT_Pin GPIO_PIN_7
#define EXP_INT_GPIO_Port GPIOD
#endif
#ifdef CHECK_WITH_NODE_IO             /* the CORE PCB rev 0.2 I/O node pins (CORE_PCB.md 14) */
#define CS_A_Pin GPIO_PIN_2
#define CS_A_GPIO_Port GPIOE
#define CS_B_Pin GPIO_PIN_3
#define CS_B_GPIO_Port GPIOE
#define CS_IN_Pin GPIO_PIN_4
#define CS_IN_GPIO_Port GPIOE
#define CS_T_Pin GPIO_PIN_15
#define CS_T_GPIO_Port GPIOE
#define CS_AI_Pin GPIO_PIN_0
#define CS_AI_GPIO_Port GPIOE
#define B_FAULT_Pin GPIO_PIN_14
#define B_FAULT_GPIO_Port GPIOD
#define B_PGOOD_Pin GPIO_PIN_15
#define B_PGOOD_GPIO_Port GPIOD
#define GATE_EN_Pin GPIO_PIN_8
#define GATE_EN_GPIO_Port GPIOB
#define WDI_Pin GPIO_PIN_9
#define WDI_GPIO_Port GPIOB
#define GATE_FB_Pin GPIO_PIN_8
#define GATE_FB_GPIO_Port GPIOD
#define PUMP_DIR_Pin GPIO_PIN_6
#define PUMP_DIR_GPIO_Port GPIOC
#define PUMP_EN_Pin GPIO_PIN_7
#define PUMP_EN_GPIO_Port GPIOC
#define REL1_N_Pin GPIO_PIN_4
#define REL1_N_GPIO_Port GPIOB
#define REL2_N_Pin GPIO_PIN_5
#define REL2_N_GPIO_Port GPIOB
#endif
#ifdef CHECK_WITH_SUPPLY
#define SUPPLY_SENSE_Pin GPIO_PIN_0
#define SUPPLY_SENSE_GPIO_Port GPIOC
#endif
#if defined(PLAT_PSRAM) && PLAT_PSRAM
#define PSRAM_XSPI_HANDLE hospi1
#endif
#ifdef CHECK_WITH_FRAM
#define FRAM_CS_Pin GPIO_PIN_4
#define FRAM_CS_GPIO_Port GPIOE
#endif
#endif
